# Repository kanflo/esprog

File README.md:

# Esprog
My ESP8266 pogo pin programmer thingy. Blog post describing the thingy [is here](http://johan.kanflo.com/factory-programming-esp8266-gadgets/).

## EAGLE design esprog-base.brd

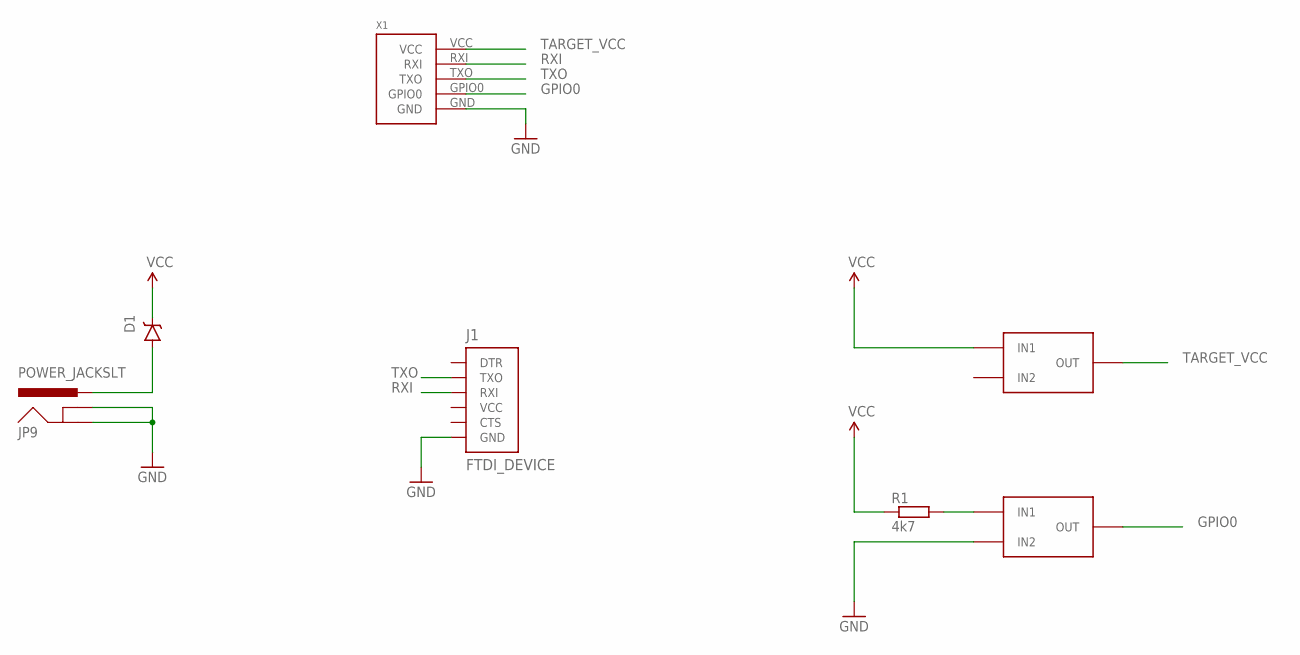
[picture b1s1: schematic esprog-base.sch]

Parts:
D1: DIODE-SCHOTTKYSOD-123FL; SOD-123FL
J1: FTDI_DEVICE; FTDI
JP9: POWER_JACKSLT; POWER_JACK_SLOT
R1: 4k7; R0603
X1: ESPROGESPROG-CONNECTOR; ESPROG-TH
X2, X3: 2WAY_SWITCHTH; 2WAY_SWITCH_TH

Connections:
GND: J1.GND, JP9.GND@1 (GNDBREAK), JP9.GND@2 (GND), X1.GND, X3.IN2_A (IN2), X3.IN2_B (IN2)
GPIO0: X1.GPIO0, X3.OUT_A (OUT), X3.OUT_B (OUT)
unnamed: R1.2, X3.IN1_A (IN1), X3.IN1_B (IN1)
unnamed: D1.A, JP9.PWR
RXI: J1.RXI, X1.RXI
TARGET_VCC: X1.VCC, X2.OUT_A (OUT), X2.OUT_B (OUT)
TXO: J1.TXO, X1.TXO
VCC: D1.C, R1.1, X2.IN1_A (IN1), X2.IN1_B (IN1)

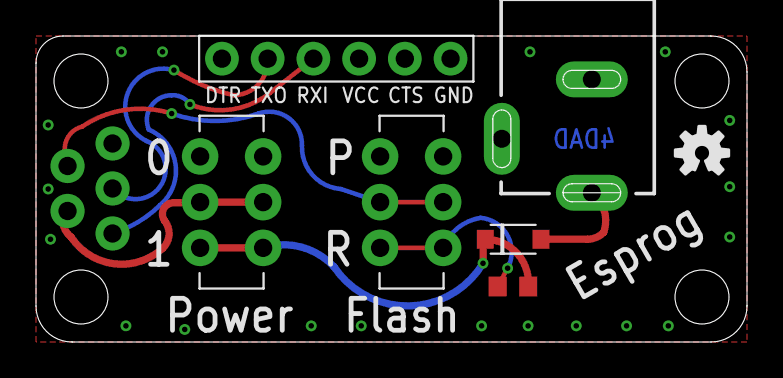
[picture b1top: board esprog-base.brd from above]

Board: 2 copper layers, 39.5 x 17.0 mm, 8 parts (0 on the bottom side), 8 nets.

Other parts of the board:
U$1: OSHW-LOGO-S

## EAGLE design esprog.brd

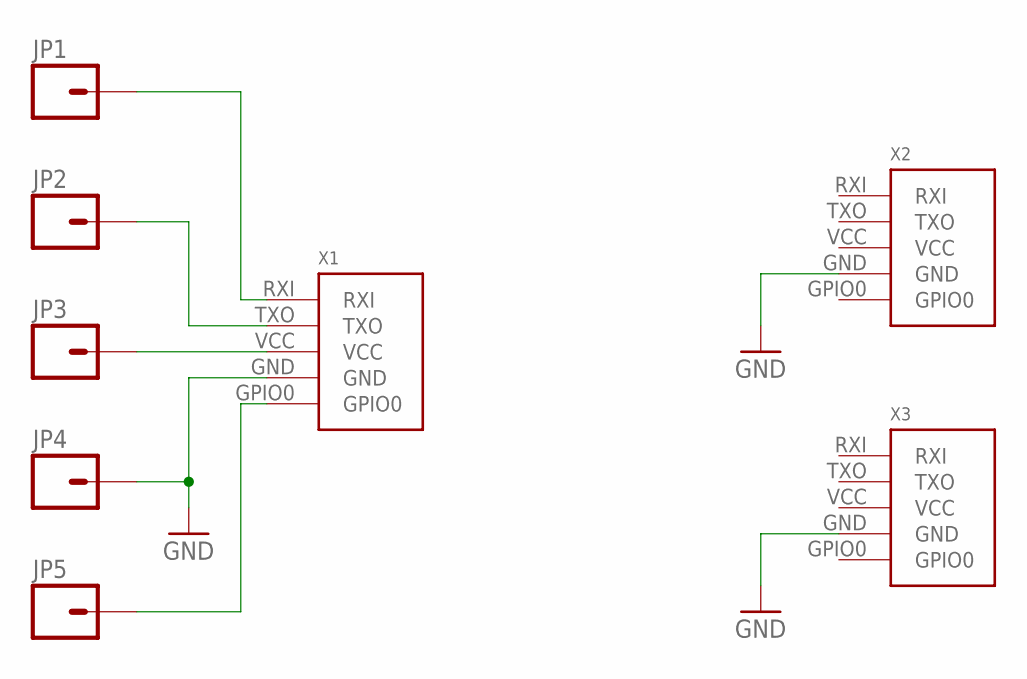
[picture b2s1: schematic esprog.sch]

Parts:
JP1, JP2, JP3, JP4, JP5: M01PTH_NO_SILK_YES_STOP; 1X01_NO_SILK
X1, X2, X3: ESPROGESPROG-CONNECTOR; ESPROG-TH

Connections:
GND: JP4.1, X1.GND, X2.GND, X3.GND
unnamed: JP1.1, X1.RXI
unnamed: JP2.1, X1.TXO
unnamed: JP3.1, X1.VCC
unnamed: JP5.1, X1.GPIO0

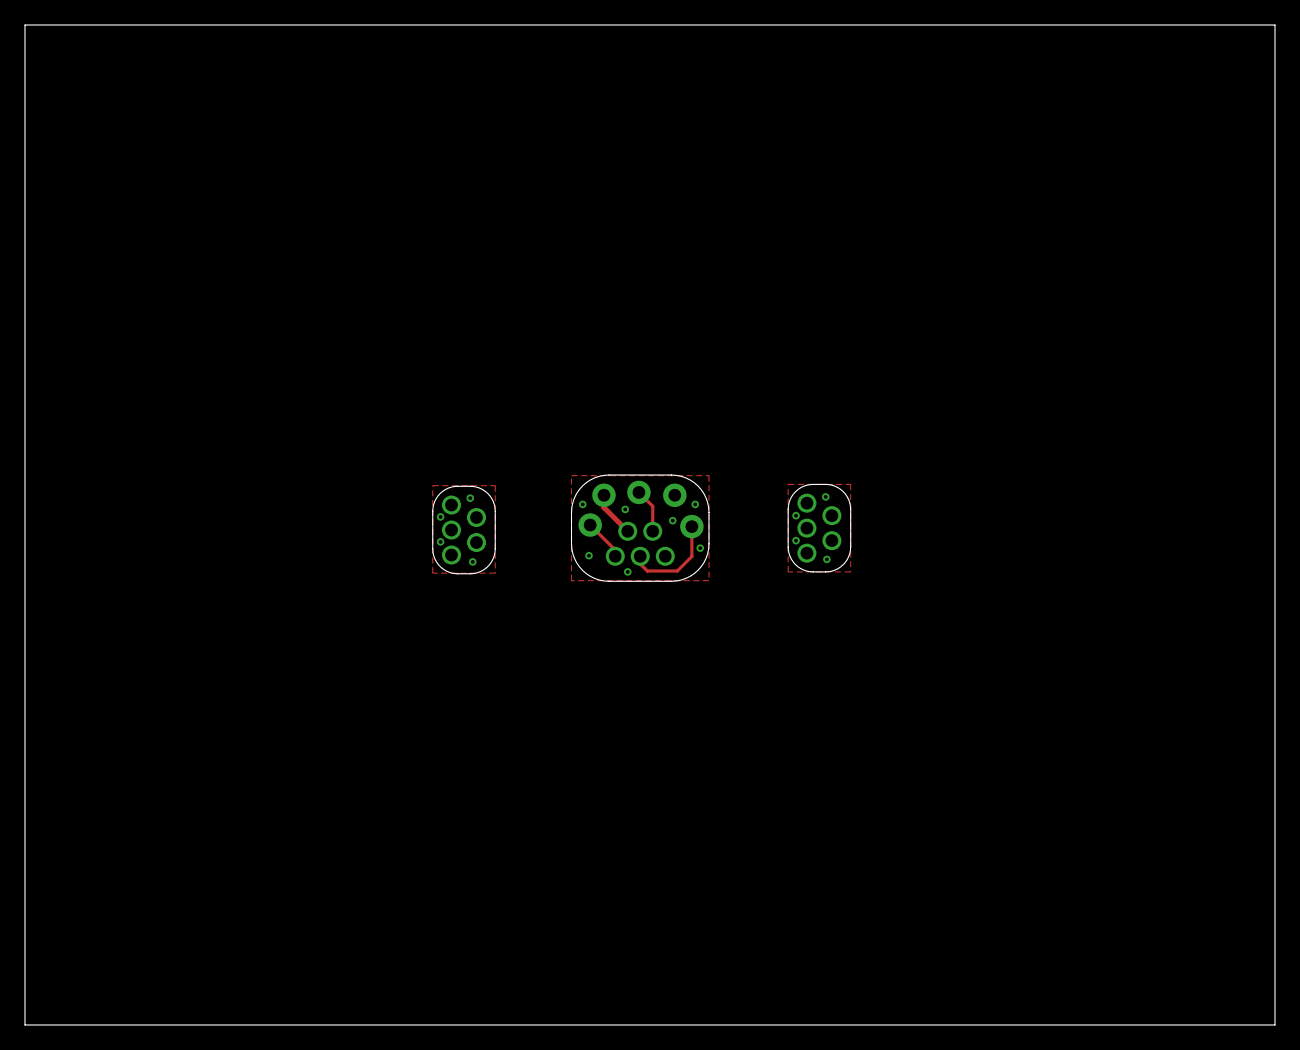
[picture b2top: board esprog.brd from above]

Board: 2 copper layers, 100.0 x 80.0 mm, 8 parts (0 on the bottom side), 5 nets.

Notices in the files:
parts and their libraries:
SparkFun-Aesthetics: Licensing: Creative Commons ShareAlike 4.0 International - https://creativecommons.org/licenses/by-sa/4.0
